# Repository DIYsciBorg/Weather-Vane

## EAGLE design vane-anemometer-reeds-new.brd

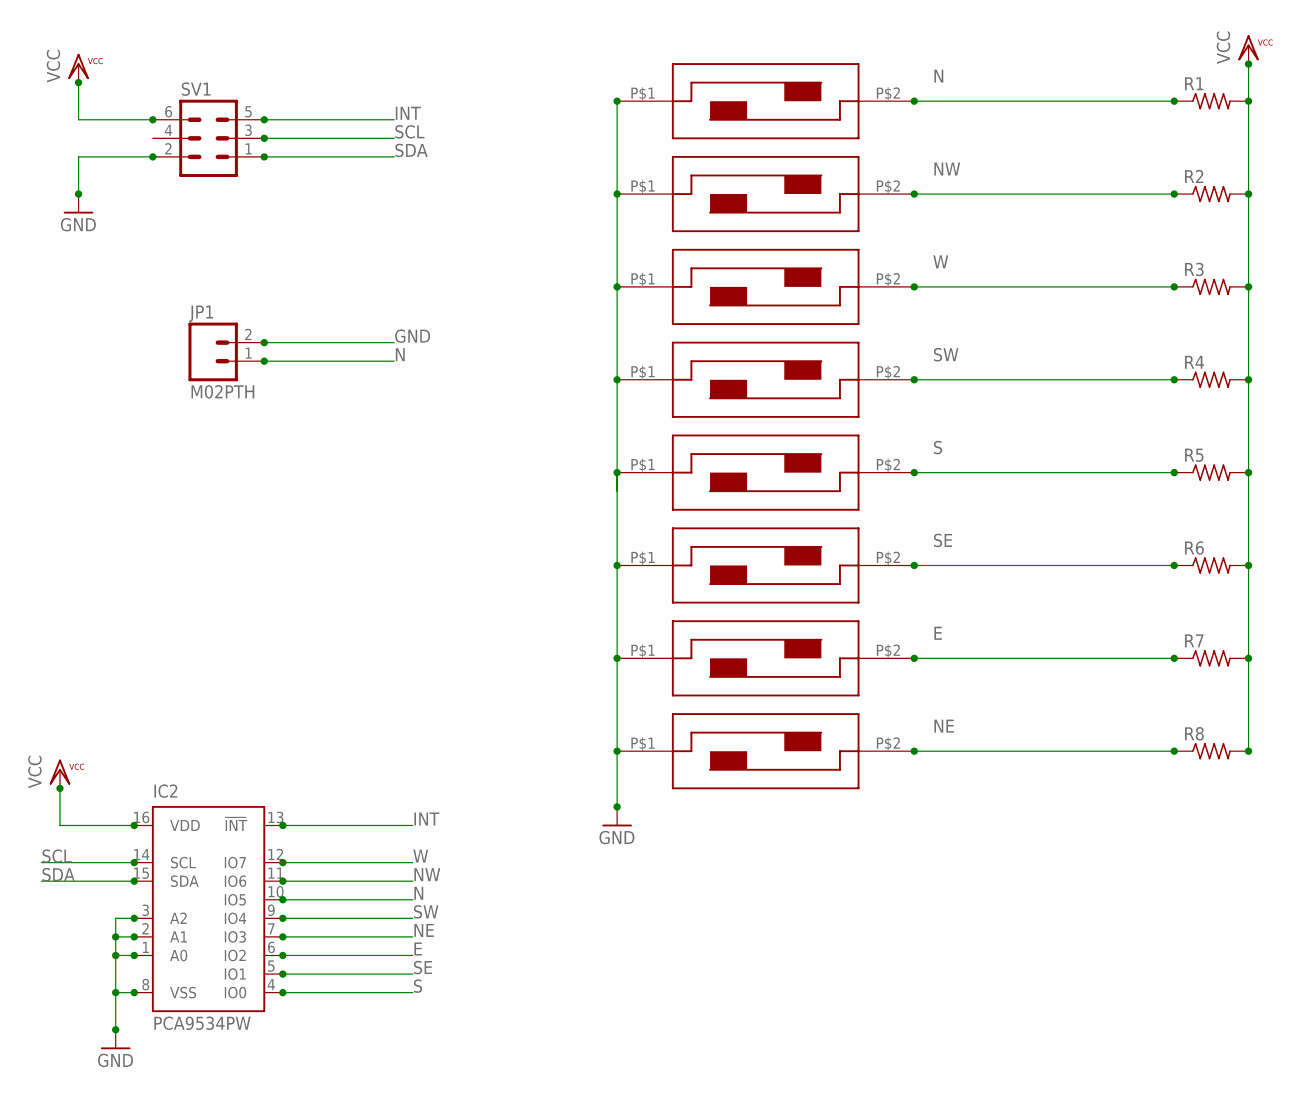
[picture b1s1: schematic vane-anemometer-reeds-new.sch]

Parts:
EAST: SP3-1A16-3A_REED_SWITCH; MKA-10110
IC2: PCA9534PW; TSSOP16
JP1: M02PTH; 1X02
NORTH: SP3-1A16-3A_REED_SWITCH; MKA-10110
NORTHEAST: SP3-1A16-3A_REED_SWITCH; MKA-10110
NORTHWEST: SP3-1A16-3A_REED_SWITCH; MKA-10110
R1, R2, R3, R4, R5, R6, R7, R8: R-US_R1005; R1005
SOUTH: SP3-1A16-3A_REED_SWITCH; MKA-10110
SOUTHEAST: SP3-1A16-3A_REED_SWITCH; MKA-10110
SOUTHWEST: SP3-1A16-3A_REED_SWITCH; MKA-10110
SV1: MA03-2
WEST: SP3-1A16-3A_REED_SWITCH; MKA-10110

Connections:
E: EAST.P$2, IC2.6 (IO2), R7.1
GND: EAST.P$1, IC2.1 (A0), IC2.2 (A1), IC2.3 (A2), IC2.8 (VSS), JP1.2, NORTH.P$1, NORTHEAST.P$1, NORTHWEST.P$1, SOUTH.P$1, SOUTHEAST.P$1, SOUTHWEST.P$1, SV1.2, WEST.P$1
INT: IC2.13 (!INT), SV1.5
N: IC2.10 (IO5), JP1.1, NORTH.P$2, R1.1
NE: IC2.7 (IO3), NORTHEAST.P$2, R8.1
NW: IC2.11 (IO6), NORTHWEST.P$2, R2.1
S: IC2.4 (IO0), R5.1, SOUTH.P$2
SCL: IC2.14 (SCL), SV1.3
SDA: IC2.15 (SDA), SV1.1
SE: IC2.5 (IO1), R6.1, SOUTHEAST.P$2
SW: IC2.9 (IO4), R4.1, SOUTHWEST.P$2
VCC: IC2.16 (VDD), R1.2, R2.2, R3.2, R4.2, R5.2, R6.2, R7.2, R8.2, SV1.6
W: IC2.12 (IO7), R3.1, WEST.P$2

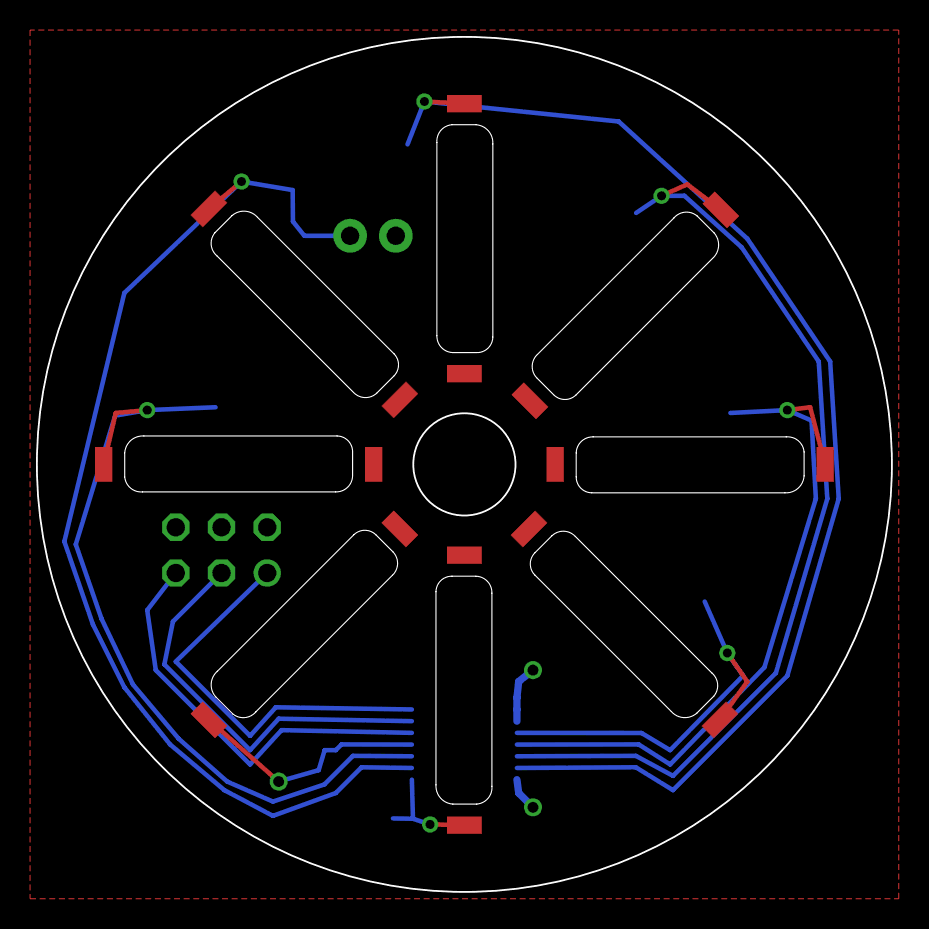
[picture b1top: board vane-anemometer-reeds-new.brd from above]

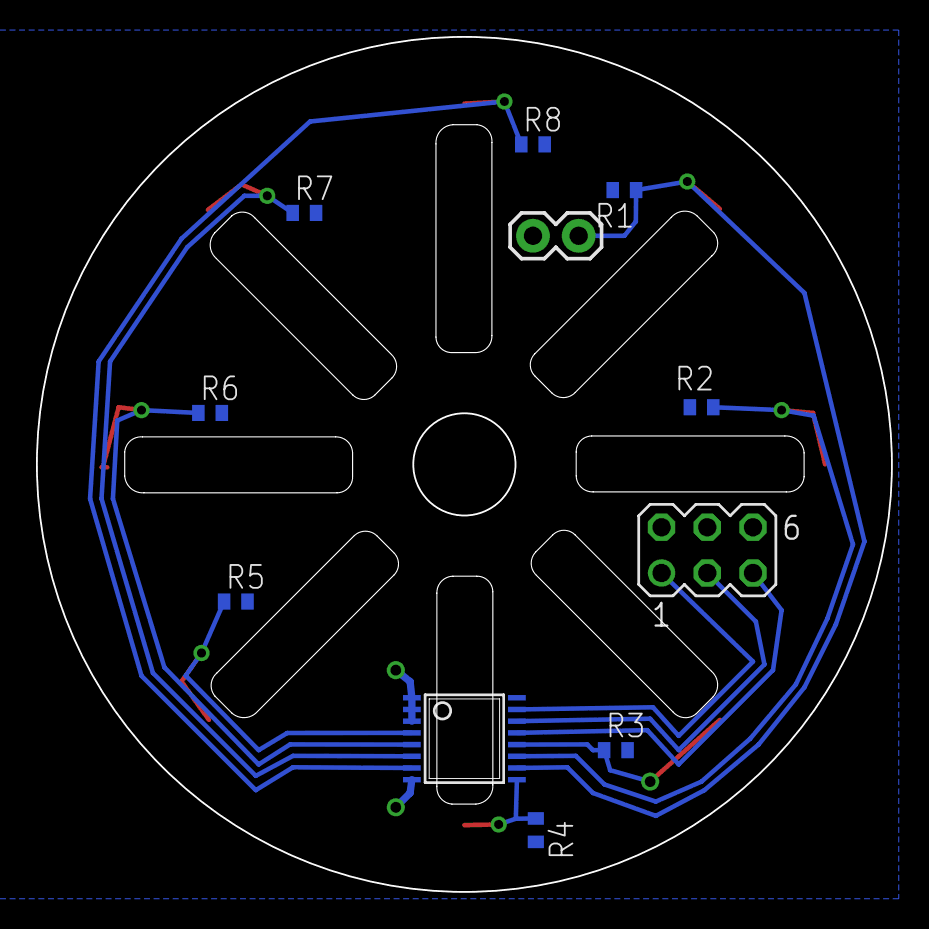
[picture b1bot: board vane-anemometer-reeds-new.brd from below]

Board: 2 copper layers, 47.5 x 47.5 mm, 19 parts (11 on the bottom side), 13 nets.

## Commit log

2014-07-13 added top and bottom images
2014-07-13 HAD update
    Added FreeCAD mechanical files, CorelDraw acrylic cut files, and lots of
    images

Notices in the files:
parts and their libraries:
SparkFun-Connectors: Licensing: CC v3.0 Share-Alike You are welcome to use this library for commercial purposes.
PatternAgents-Beautify: License : http://creativecommons.org/licenses/by-sa/3.0
(Creative Commons 3.0)
